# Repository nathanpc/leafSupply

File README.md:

## More Information

For more information about how this project evolved you should check out the [project blog](http://electronics.dreamintech.net/).

## Credits

This project is the work of:

 - [Nathan Campos](http://about.me/nathanpc): Everything involved with the electronics part.
 - [Narek Babajanyan](https://twitter.com/narekb): Awesome leaf icon.

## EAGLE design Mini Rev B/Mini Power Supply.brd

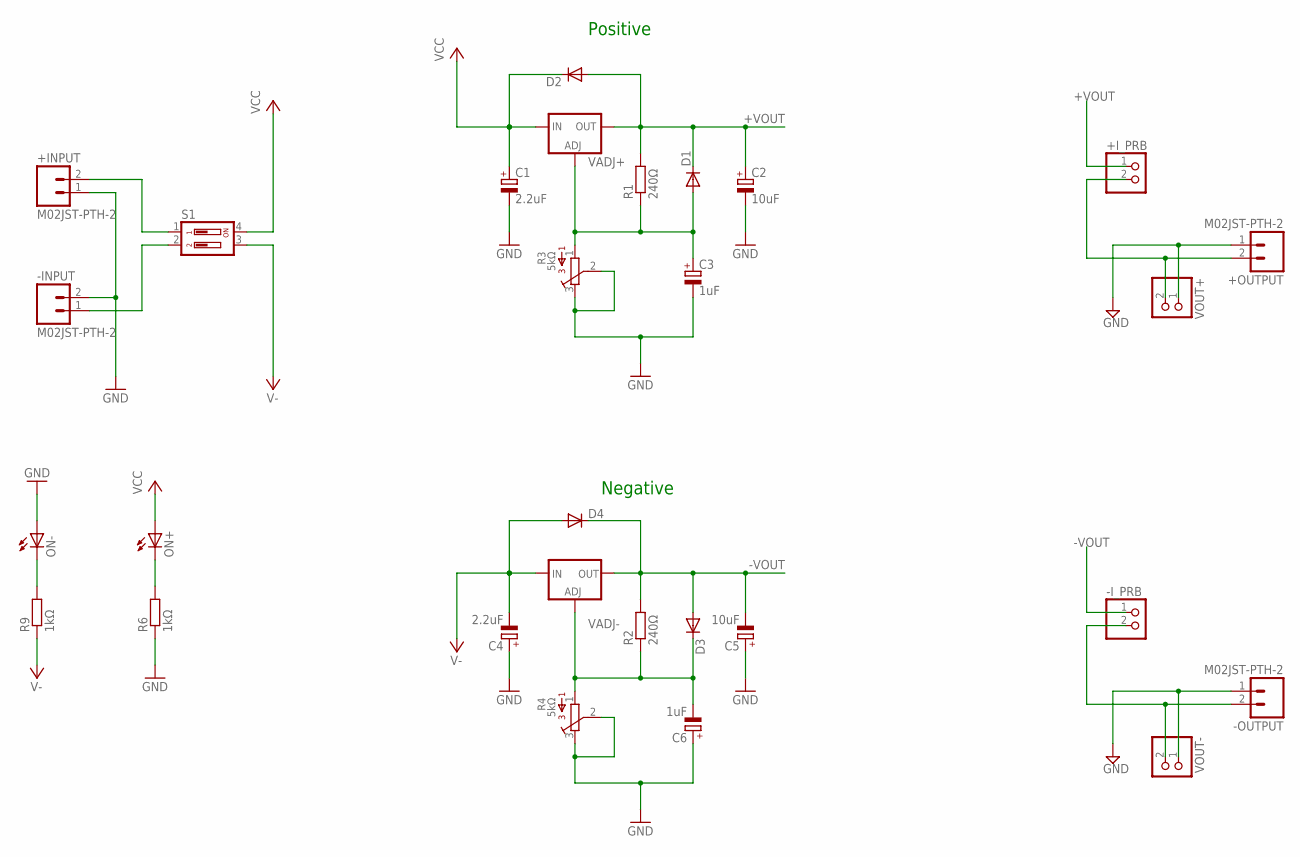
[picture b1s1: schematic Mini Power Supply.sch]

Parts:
+INPUT: M02JST-PTH-2; JST-2-PTH
+I_PRB: PINHD-1X2; 1X02
+OUTPUT: M02JST-PTH-2; JST-2-PTH
-INPUT: M02JST-PTH-2; JST-2-PTH
-I_PRB: PINHD-1X2; 1X02
-OUTPUT: M02JST-PTH-2; JST-2-PTH
C1, C4: 2.2uF; E2,5-6
C2, C5: 10uF; E2,5-6
C3, C6: 1uF; E2,5-6
D1, D2, D3, D4: 1N4148DO35-7; DO35-7
ON+: LEDSQR2X5; LED2X5
ON-: LEDSQR2X5; LED2X5
R1, R2: 240Ω; 0207/10
R3, R4: 5kΩ; 3386U
R6, R9: 1kΩ; 0207/10
S1: DIP02YL
VADJ+: LM317L; 317L
VADJ-: LM337L; 337L
VOUT+: PINHD-1X2; 1X02
VOUT-: PINHD-1X2; 1X02

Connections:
+VOUT: +I_PRB.1, C2.+, D1.C, D2.A, R1.2, VADJ+.2 (OUT)
-VOUT: -I_PRB.1, C5.-, D3.A, D4.C, R2.2, VADJ-.OUT
GND: +INPUT.1, +OUTPUT.1, -INPUT.2, -OUTPUT.1, C1.-, C2.-, C3.-, C4.+, C5.+, C6.+, ON-.A, R3.2, R3.3, R4.2, R4.3, R6.1, VOUT+.1, VOUT-.1
unnamed: C6.-, D3.C, R2.1, R4.1, VADJ-.ADJ
unnamed: +INPUT.2, S1.1
unnamed: C3.+, D1.A, R1.1, R3.1, VADJ+.1 (ADJ)
unnamed: ON-.K (C), R9.2
unnamed: -INPUT.1, S1.2
unnamed: ON+.K (C), R6.2
unnamed: +I_PRB.2, +OUTPUT.2, VOUT+.2
unnamed: -I_PRB.2, -OUTPUT.2, VOUT-.2
V-: C4.-, D4.A, R9.1, S1.3, VADJ-.IN
VCC: C1.+, D2.C, ON+.A, S1.4, VADJ+.3 (IN)

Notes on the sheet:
Positive
Negative

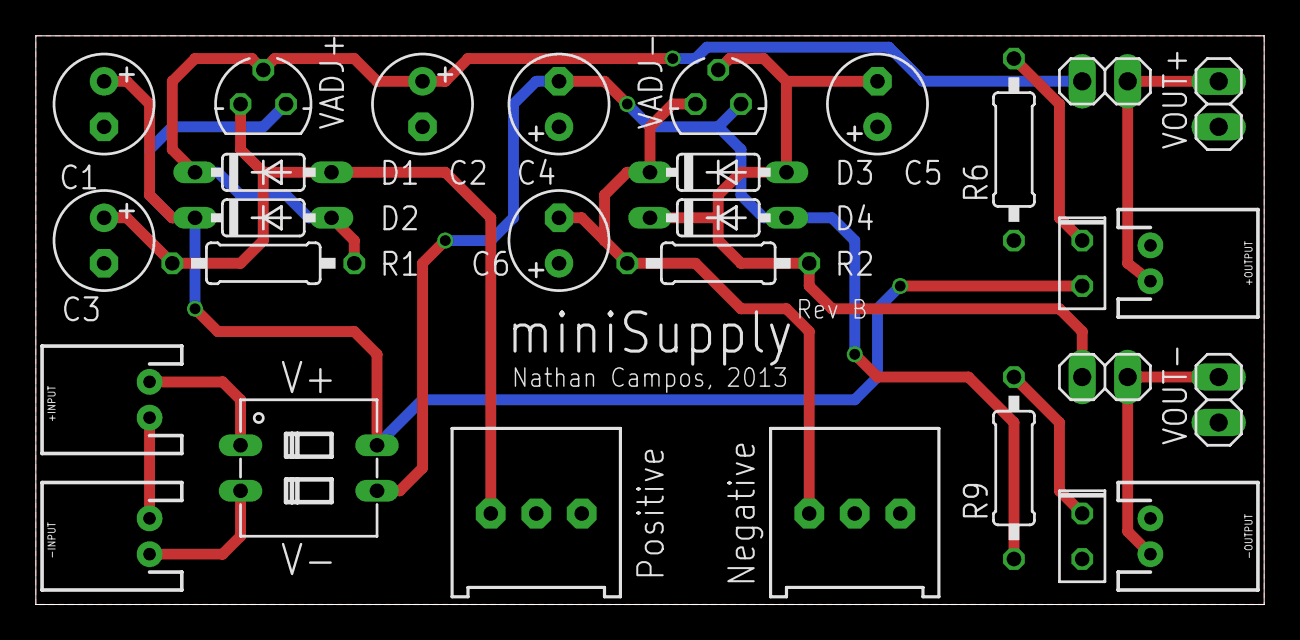
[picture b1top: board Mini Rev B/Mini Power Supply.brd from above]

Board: 4 copper layers, 68.6 x 31.8 mm, 29 parts (0 on the bottom side), 13 nets.

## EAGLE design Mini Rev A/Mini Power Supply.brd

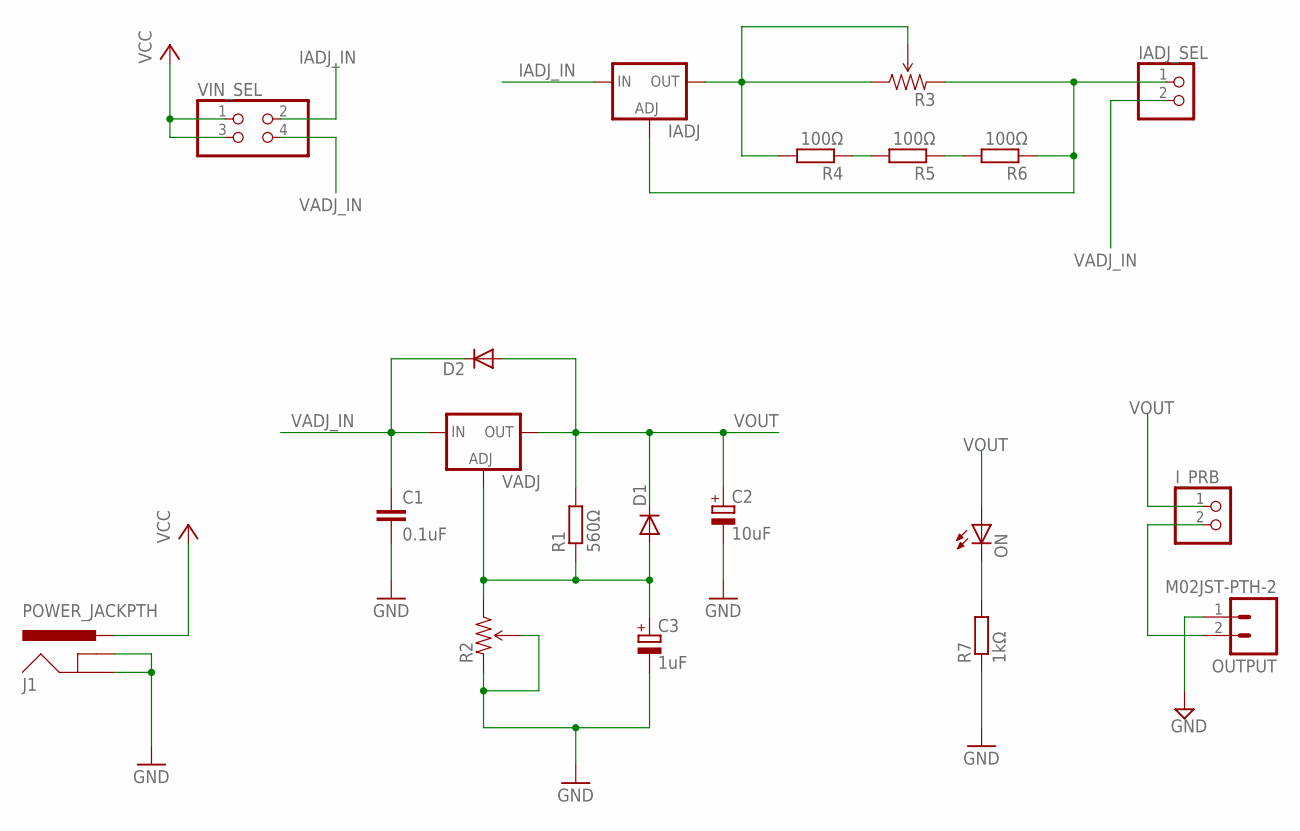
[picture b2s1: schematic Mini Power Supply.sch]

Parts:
C1: 0.1uF; C0805
C2: 10uF; E2,5-6
C3: 1uF; E2,5-6
D1, D2: DIODE-SOD323-W; SOD323-W
IADJ: LM317TS; 317TS
IADJ_SEL: PINHD-1X2; 1X02
I_PRB: PINHD-1X2; 1X02
J1: POWER_JACKPTH; POWER_JACK_PTH
ON: LEDCHIPLED_1206; CHIPLED_1206
OUTPUT: M02JST-PTH-2; JST-2-PTH
R1: 560Ω; R0805
R2, R3: TRIMPOT-PTH-KNOB; 3386U
R4, R5, R6: 100Ω; R0805
R7: 1kΩ; R0805
VADJ: LM317TS; 317TS
VIN_SEL: PINHD-2X2; 2X02

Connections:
GND: C1.2, C2.-, C3.-, J1.GND, J1.GNDBREAK, OUTPUT.1, R2.2 (WIPER), R2.3 (CW), R7.1
IADJ_IN: IADJ.3 (IN), VIN_SEL.2
unnamed: IADJ.2 (OUT), R3.1 (CCW), R3.2 (WIPER), R4.2
unnamed: R4.1, R5.2
unnamed: C3.+, D1.A, R1.1, R2.1 (CCW), VADJ.1 (ADJ)
unnamed: IADJ.1 (ADJ), IADJ_SEL.1, R3.3 (CW), R6.1
unnamed: R5.1, R6.2
unnamed: ON.C, R7.2
unnamed: I_PRB.2, OUTPUT.2
VADJ_IN: C1.1, D2.C, IADJ_SEL.2, VADJ.3 (IN), VIN_SEL.4
VCC: J1.PWR, VIN_SEL.1, VIN_SEL.3
VOUT: C2.+, D1.C, D2.A, I_PRB.1, ON.A, R1.2, VADJ.2 (OUT)

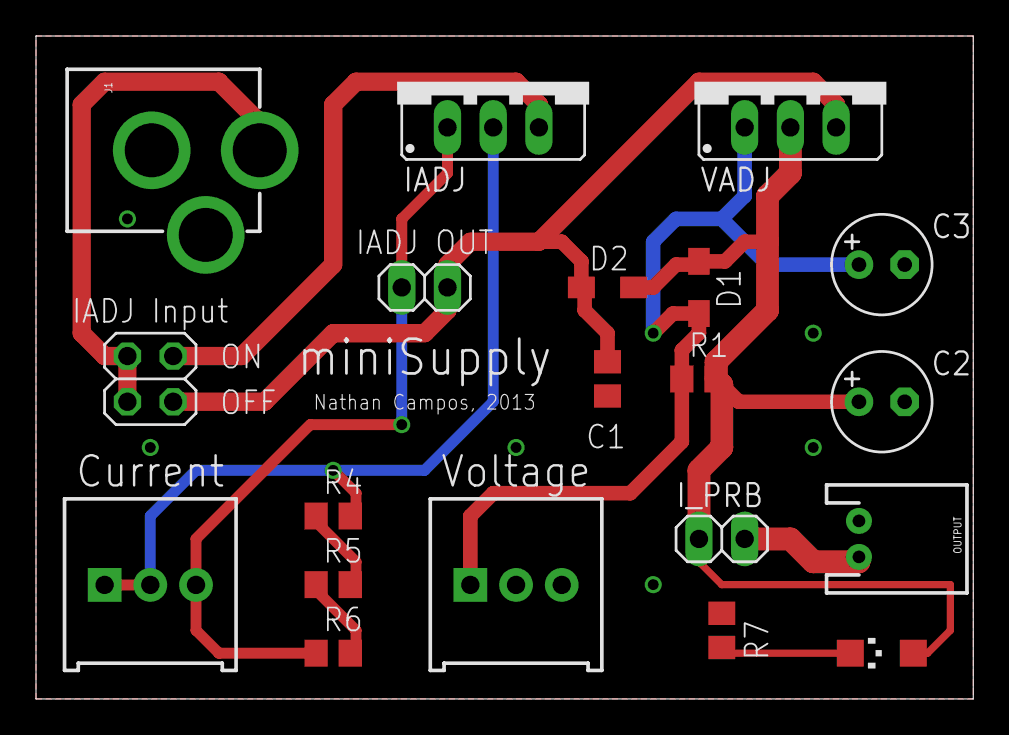
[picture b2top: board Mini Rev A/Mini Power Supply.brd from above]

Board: 2 copper layers, 52.1 x 36.8 mm, 20 parts (0 on the bottom side), 12 nets.

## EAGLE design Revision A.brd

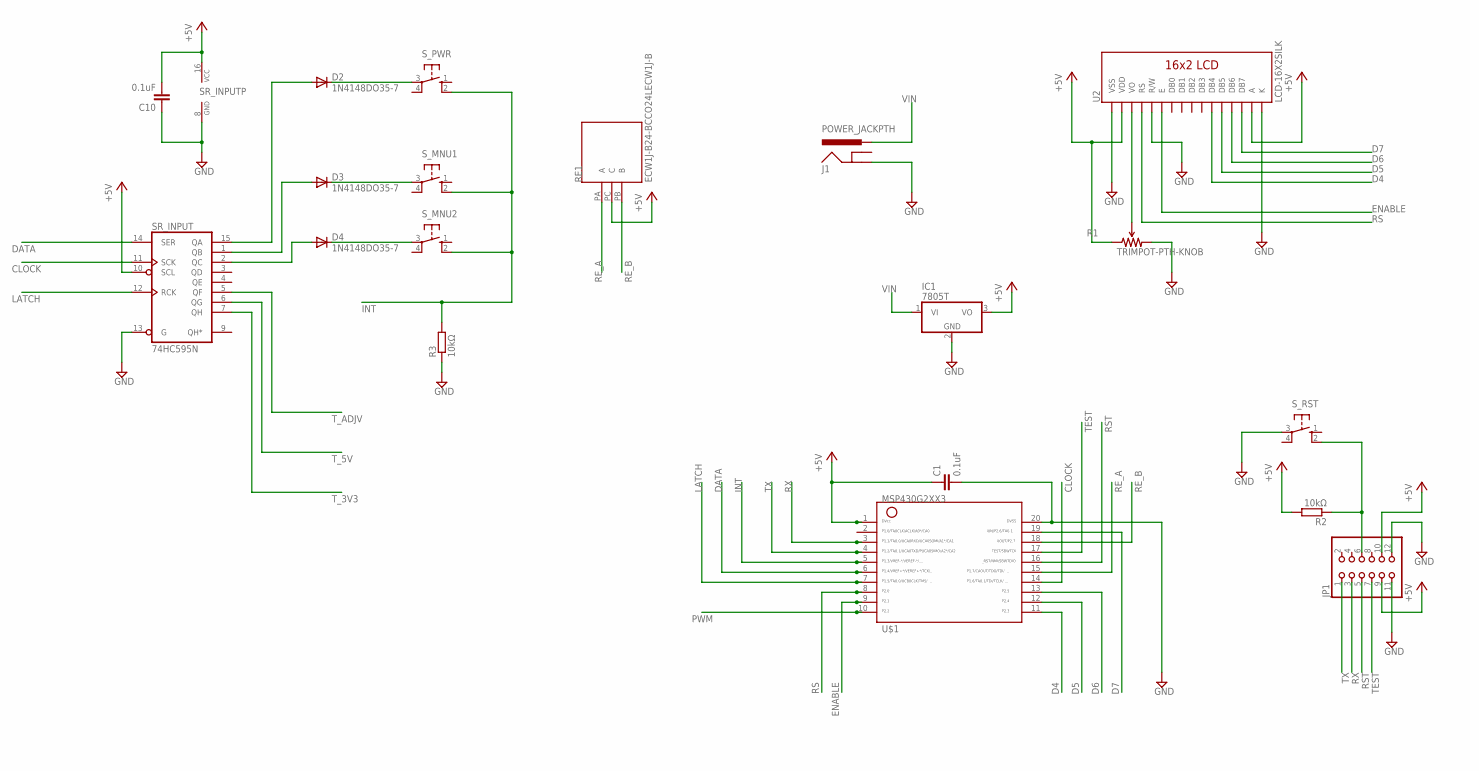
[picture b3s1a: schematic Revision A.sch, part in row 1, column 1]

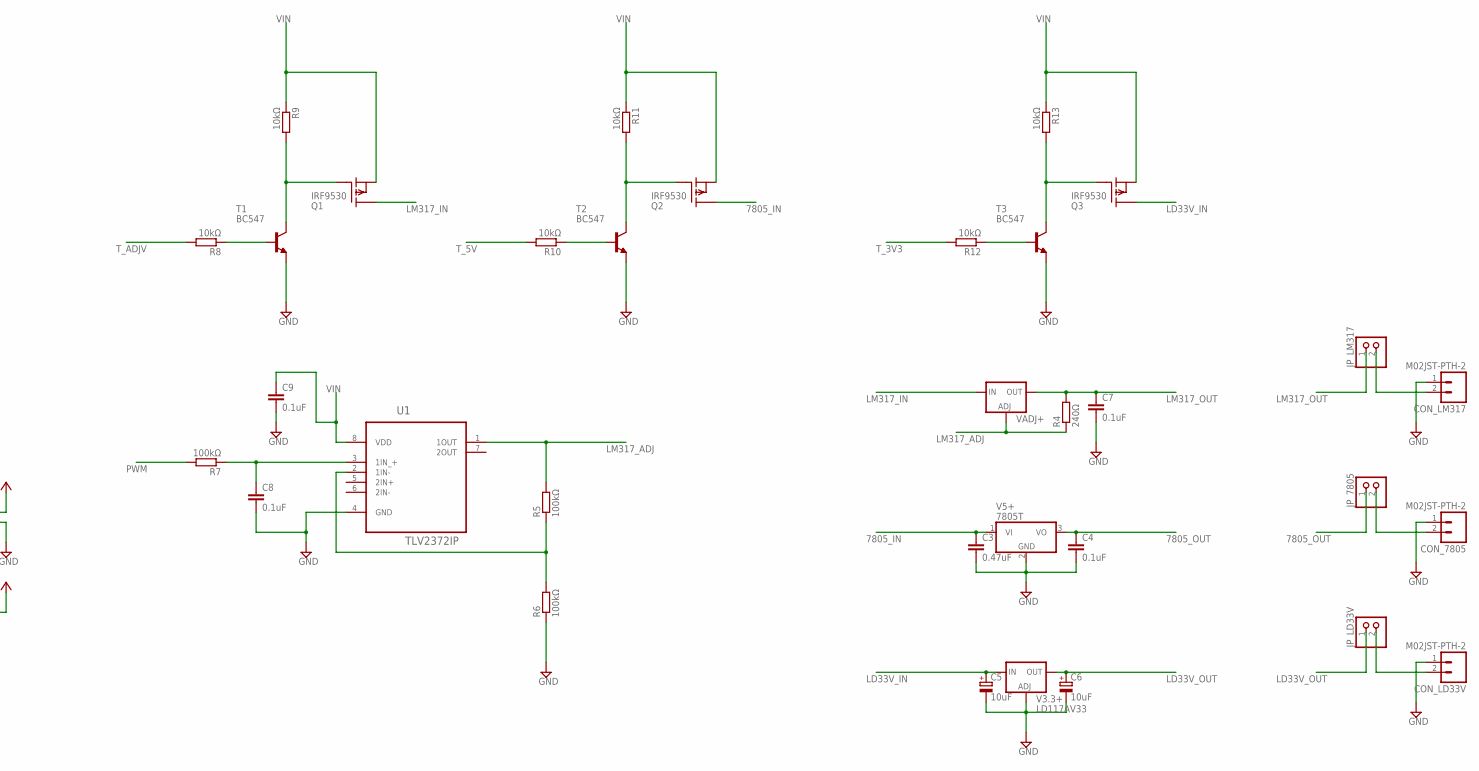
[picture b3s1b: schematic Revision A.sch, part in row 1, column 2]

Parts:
C1, C4, C7, C8, C9, C10: 0.1uF; C025-025X050
C3: 0.47uF; C025-025X050
C5, C6: 10uF; E2,5-6
CON_7805: M02JST-PTH-2; JST-2-PTH
CON_LD33V: M02JST-PTH-2; JST-2-PTH
CON_LM317: M02JST-PTH-2; JST-2-PTH
D2, D3, D4: 1N4148DO35-7; DO35-7
IC1: 7805T; TO220H
J1: POWER_JACKPTH; POWER_JACK_PTH
JP1: PINHD-2X6; 2X06
JP_7805: PINHD-1X2; 1X02
JP_LD33V: PINHD-1X2; 1X02
JP_LM317: PINHD-1X2; 1X02
Q1, Q2, Q3: IRF9530; TO220
R1: TRIMPOT-PTH-KNOB; 3386U
R2, R3, R8, R9, R10, R11, R12, R13: 10kΩ; 0207/10
R4: 240Ω; 0207/10
R5, R6, R7: 100kΩ; 0207/10
RE1: ECW1J-B24-BCCO24LECW1J-B; ECW1J-B
SR_INPUT: 74HC595N; DIL16
S_MNU1, S_MNU2: 10-XX; B3F-10XX
S_PWR: 10-XX; B3F-10XX
S_RST: 10-XX; B3F-10XX
T1, T2, T3: BC547; TO92
U1: TLV2372IP; DIP254P762X508-8
U2: LCD-16X2SILK; LCD-16X2
U$1: G2XX3---N20; N20
V3.3+: LD117AV33; TO220L1
V5+: 7805T; TO220H
VADJ+: LM317TL; 317TL

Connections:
7805_IN: C3.1, Q2.2 (D), V5+.1 (VI)
7805_OUT: C4.1, JP_7805.1, V5+.3 (VO)
+5V: C1.1, C10.2, IC1.3 (VO), JP1.9, JP1.10, R1.1 (CCW), R2.2, RE1.PC (C), SR_INPUT.10 (SCL), SR_INPUT.16 (VCC), U2.2 (VDD), U2.15 (A), U$1.1
CLOCK: SR_INPUT.11 (SCK), U$1.14
D4: U2.11 (DB4), U$1.11
D5: U2.12 (DB5), U$1.12
D6: U2.13 (DB6), U$1.13
D7: U2.14 (DB7), U$1.19
DATA: SR_INPUT.14 (SER), U$1.6
ENABLE: U2.6 (E), U$1.9
GND: C1.2, C3.2, C4.2, C5.-, C6.-, C7.2, C8.2, C9.2, C10.1, CON_7805.1, CON_LD33V.1, CON_LM317.1, IC1.2 (GND), J1.GND, JP1.11, JP1.12, R1.3 (CW), R3.1, R6.1, SR_INPUT.8 (GND), SR_INPUT.13 (G), S_RST.3, T1.1 (E), T2.1 (E), T3.1 (E), U1.4 (GND), U2.1 (VSS), U2.5 (R/W), U2.16 (K), U$1.20, V3.3+.1 (ADJ), V5+.2 (GND)
INT: R3.2, S_MNU1.2 (S1), S_MNU2.2 (S1), S_PWR.2 (S1), U$1.5
LATCH: SR_INPUT.12 (RCK), U$1.7
LD33V_IN: C5.+, Q3.2 (D), V3.3+.3 (IN)
LD33V_OUT: C6.+, JP_LD33V.1, V3.3+.2 (OUT)
LM317_ADJ: R4.1, R5.2, U1.1 (1OUT), VADJ+.1 (ADJ)
LM317_IN: Q1.2 (D), VADJ+.3 (IN)
LM317_OUT: C7.1, JP_LM317.1, R4.2, VADJ+.2 (OUT)
unnamed: R1.2 (WIPER), U2.3 (VO)
unnamed: D2.C, S_PWR.3
unnamed: JP1.6, R2.1, S_RST.2 (S1)
unnamed: D3.C, S_MNU1.3
unnamed: D4.C, S_MNU2.3
unnamed: R5.1, R6.2, U1.2 (1IN-)
unnamed: C8.1, R7.1, U1.3 (1IN_+)
unnamed: R8.1, T1.2 (B)
unnamed: Q1.1 (G), R9.2, T1.3 (C)
unnamed: R10.1, T2.2 (B)
unnamed: D3.A, SR_INPUT.1 (QB)
unnamed: Q2.1 (G), R11.2, T2.3 (C)
unnamed: R12.1, T3.2 (B)
unnamed: Q3.1 (G), R13.2, T3.3 (C)
unnamed: CON_LM317.2, JP_LM317.2
unnamed: D4.A, SR_INPUT.2 (QC)
unnamed: D2.A, SR_INPUT.15 (QA)
unnamed: CON_7805.2, JP_7805.2
unnamed: CON_LD33V.2, JP_LD33V.2
PWM: R7.2, U$1.10
RE_A: RE1.PA (A), U$1.15
RE_B: RE1.PB (B), U$1.18
RS: U2.4 (RS), U$1.8
RST: JP1.5, U$1.16
RX: JP1.3, U$1.3
TEST: JP1.7, U$1.17
TX: JP1.1, U$1.4
T_3V3: R12.2, SR_INPUT.7 (QH)
T_5V: R10.2, SR_INPUT.6 (QG)
T_ADJV: R8.2, SR_INPUT.5 (QF)
VIN: C9.1, IC1.1 (VI), J1.PWR, Q1.3 (S), Q2.3 (S), Q3.3 (S), R9.1, R11.1, R13.1, U1.8 (VDD)

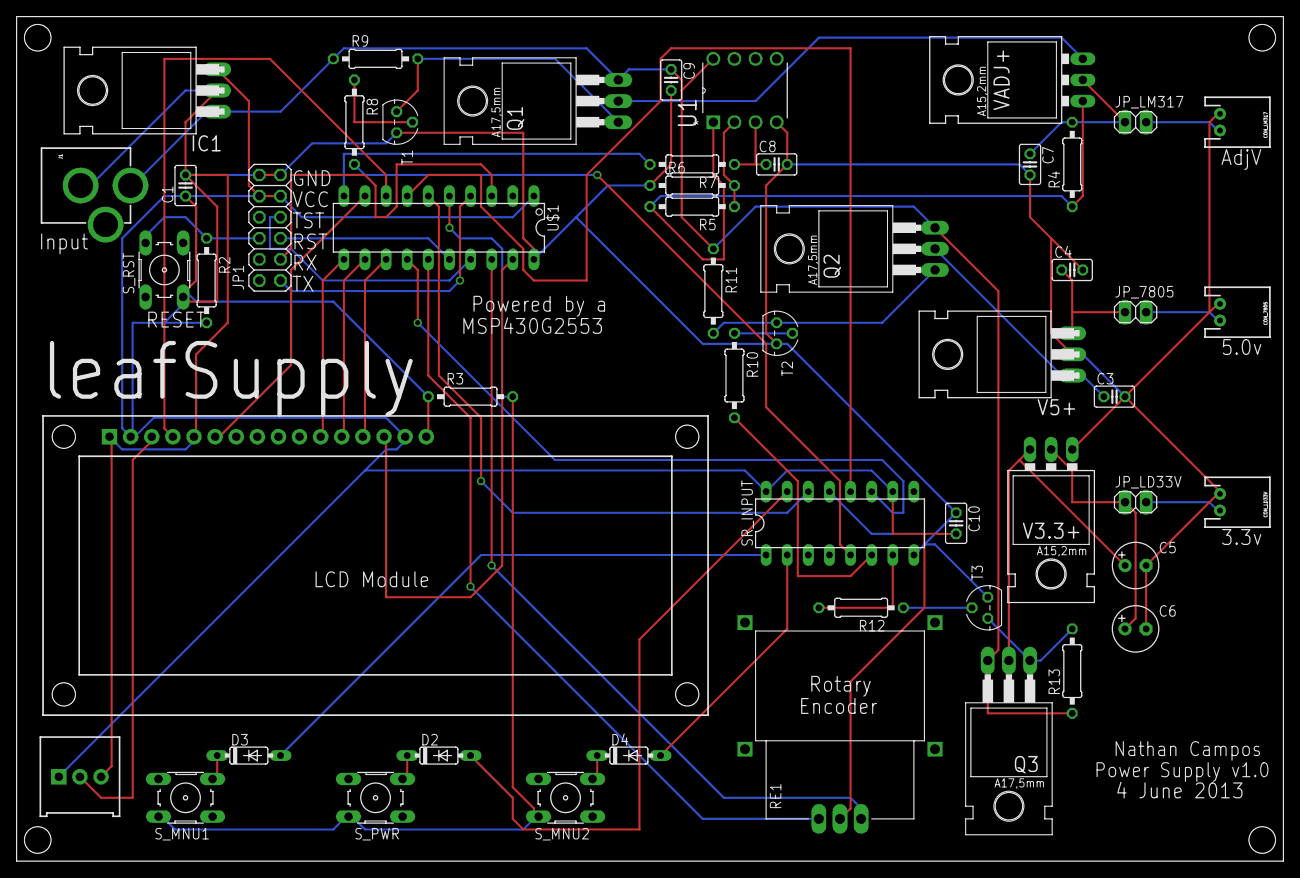
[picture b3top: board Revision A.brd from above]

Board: 2 copper layers, 152.4 x 101.6 mm, 52 parts (0 on the bottom side), 49 nets.

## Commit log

2013-05-24 First crappy draft stuff
2013-05-24 "An" instead of "A"
2013-05-24 Oops, typo
2013-05-25 Added the project requirements document
2013-05-25 Added information about the requirements document
2013-05-25 Brainstorming the LCD firmware interface
2013-05-26 Removed the digital potentiometer in favor of PWM control to use less pins
2013-05-26 Started working in the microcontroller part
2013-05-28 Updated the README and included some logos
2013-05-30 Removed the black logo since it's only used in the README
2013-05-30 Oops, looks like my pin count was wrong
2013-05-30 Added information about the microcontroller and the output logic
2013-05-30 Added the Output Logic schematic
2013-05-30 Added a truth table to the output logic schematic
2013-06-01 Removed the requirements.md in favor of the project blog
2013-06-01 Started working in the new Shift Register oriented design
2013-06-01 Finished the shift register oriented design schematic
2013-06-01 Added some decoupling capacitors
2013-06-04 Renamed the Logo directory
2013-06-04 Started working in the firmware
2013-06-05 Added *.elf files to the .gitignore
2013-06-05 Improved the shift register design since we are going to use a rotary encoder
2013-06-05 Core firmware test finished
2013-06-05 Added support for setting the LCD cursor position
2013-06-06 Added a ftoa implementation
2013-06-06 Implemented a line/col print function
2013-06-06 Things are starting to look more like how they are supposed to be
2013-06-06 Started working in the output logic
2013-06-06 Removed the old individual test stuff
2013-06-06 Commented the code a lot more
2013-06-08 Working with PWM
2013-06-09 Finished all the voltage control stuff
2013-06-10 Removed a button
2013-06-10 Finished the output schematic
2013-06-10 Removed all the outdated crappy microcontroller drafts
2013-06-10 Added the LCD schematic
2013-06-11 Finished the individual schematics
2013-06-11 Fixed some errors
2013-06-11 Used the awesome SparkFun LCD footprint
2013-06-11 Ignoring all .*#*
2013-06-11 Created a custom library for the rotary encoder footprint
2013-06-11 Added the rotary encoder to the mix
2013-06-11 Added the full schematic for Rev A
2013-06-11 Removed the brainstorming stuff
2013-06-11 Made things look nicer for print
2013-06-11 Updated the README
2013-06-11 Renamed the Microcontroller Draft folder to Rev A
2013-06-13 Checked
2013-06-14 Added the input barrel jack
2013-06-14 Board designed
2013-06-14 Finished the silkscreen stuff
2013-06-14 Fixed the RESET pin connection
2013-07-11 Fixed the voltage regulator for the MCU
2013-07-11 Moved everything related to the Rev A to its folder so we can start working on Rev B
2013-08-23 Designed a mini version
2013-09-08 Started working on Rev B of the mini
2013-09-08 Changed the input to a JST and connected the ON LED to VCC
2013-09-10 Finished most of the new revision
2013-09-13 Started working on the negative rail for the mini Rev B
2013-09-13 Finished the negative rail
2013-10-15 Redid the Mini Rev B
2013-10-15 Finished the layout for Mini Rev B
2013-10-15 Removed the Rev A information from the README
2013-11-03 Fixed the negative voltage regulator
2013-11-10 Started working on Mini Rev C

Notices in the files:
parts and their libraries:
SparkFun-Electromechanical: Licensing: CC v3.0 Share-Alike You are welcome to use this library for commercial purposes.
